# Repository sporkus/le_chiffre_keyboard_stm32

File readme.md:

# Le Chiffre Keyboard - STM32 version
-----------

Open sourced PCB originally design by tominabox1 updated to STM32 MCU.

## Design goals
* Drop-in replacement to existing cases
* MCU: STM32F072CBT6 (128Kb flash, built-in DFU bootloader) to allow more firmware features
* MX hotswap, Alps support
* Optional 36 key support

## Firmware
* [QMK and vial source](./firmware)
* [zmk config](https://github.com/petejohanson/le-chiffre-stm32-zmk-config)
* [pre-compiled vial](./firmware/le_chiffre_32_vial.bin)

To flash initially using dfu-util or qmk toolbox, plug in the board or push the reset button while DFU button is held down.

## Fabrication
* verified production files can be found [here](./pcb_production)
* pcb dimensions: 84.96x227.34mm
* SK6812 mini 3535 has placement marker on "Data In" pin. Don't confuse it with sk6812-HS mini or sk6812 mini-E.

## Misc
#### 3D assembly preview
* [online viewer](https://3dviewer.net/#model=https://github.com/sporkus/le_chiffre_keyboard_stm32/blob/main/documentation/stm32_hotswap_chiffre-3D.step)
* [step assembly](./documentation/stm32_hotswap_chiffre-3D.step)

#### PCB renders

#### BoM
[interactive BoM](./documentation/stm32_hotswap_chiffre-ibom.html)

#### Schematic
[Schematic pdf](./documentation/stm32_hotswap_chiffre-schematic.pdf)

#### Case

## Credits
tominabox1 for the [original design](https://github.com/tominabox1/Le-Chiffre-Keyboard)

## Changelog
* v0.3.0: add optional 36 key support
* v0.2.2: change center switch to soldered instead of hotswap. Group buy.
* v0.2.1: added front led bypass jumper
* v0.2.0: improved protection circuit
* v0.1: working initial prototypes

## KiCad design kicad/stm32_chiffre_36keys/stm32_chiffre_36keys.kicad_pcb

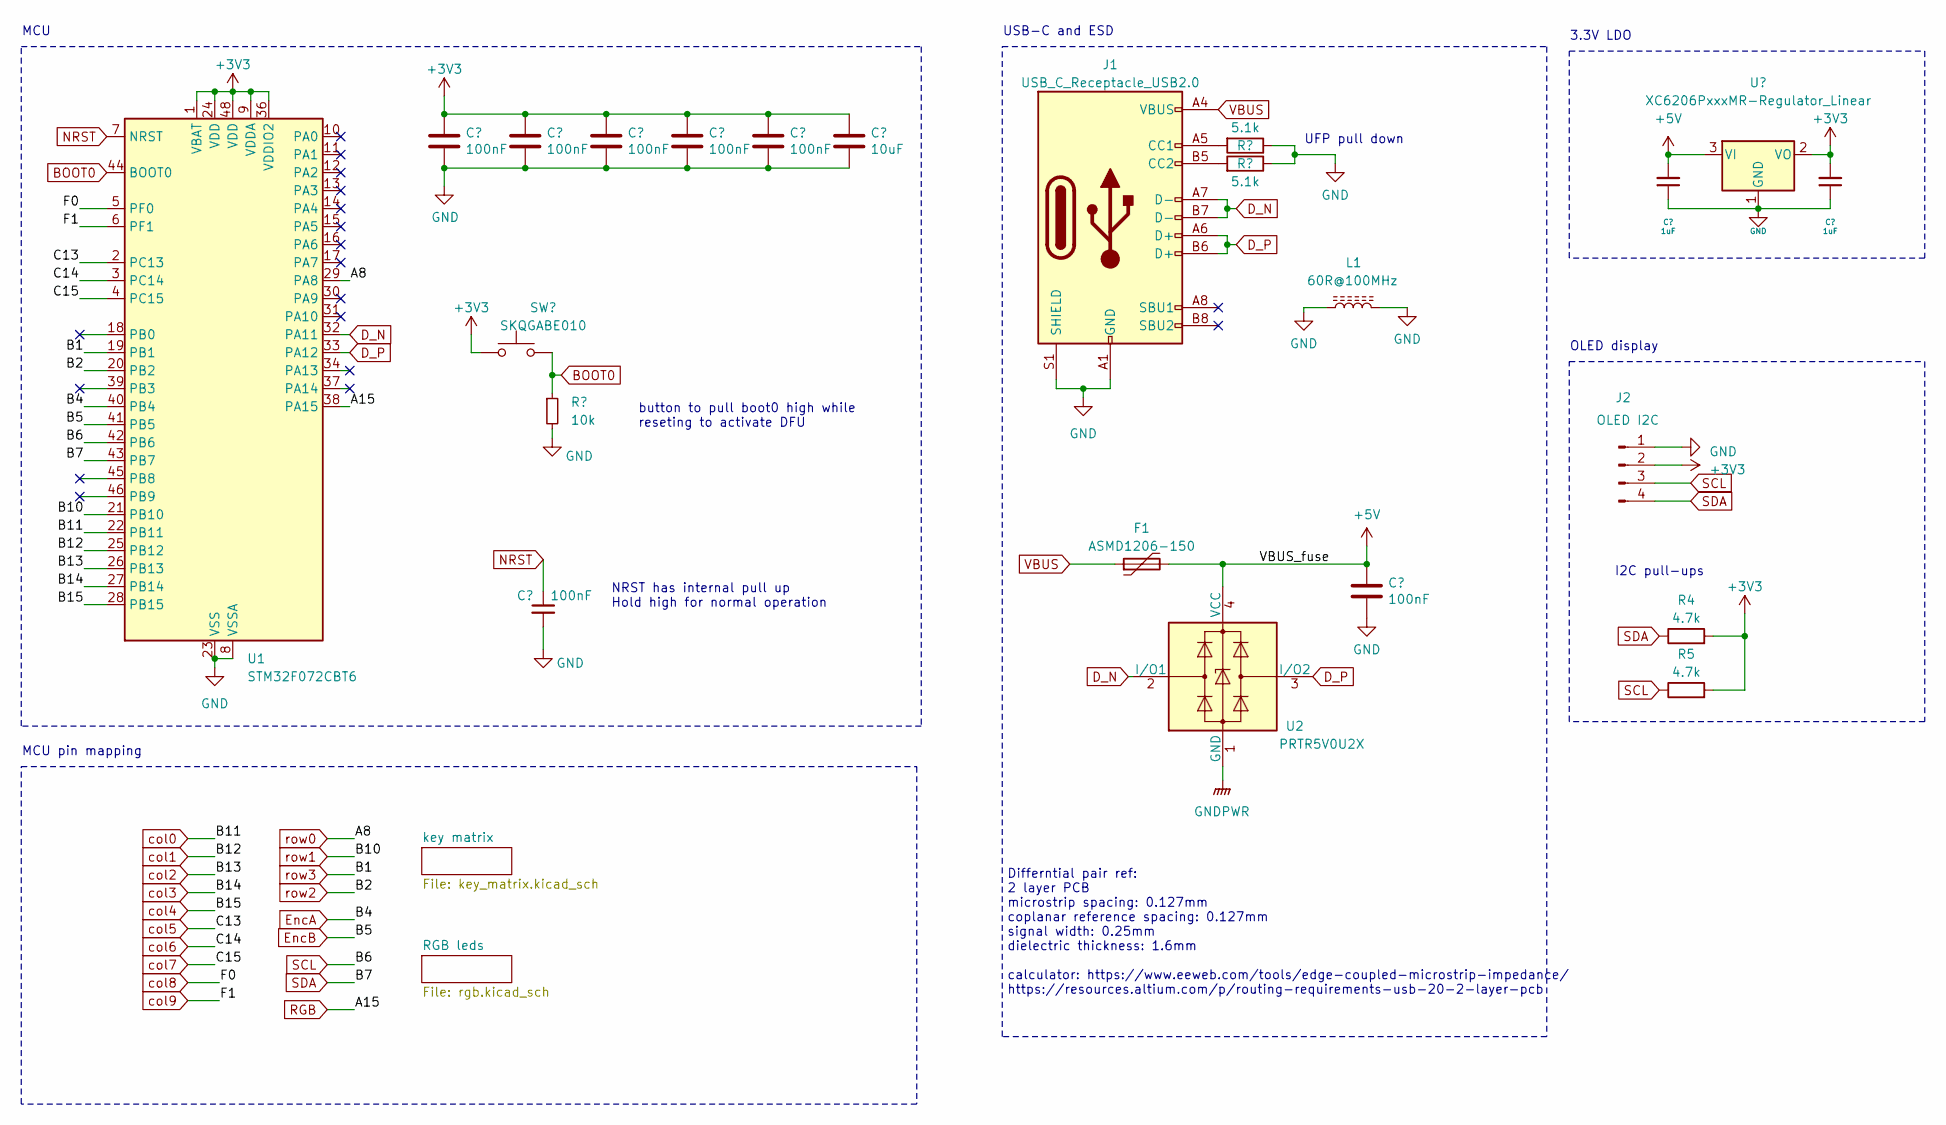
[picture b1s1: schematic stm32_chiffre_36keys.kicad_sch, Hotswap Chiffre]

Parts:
C1, C2, C3, C4, C5, C7, C8: 100nF; C_0402_1005Metric; LCSC C307331
C6: 10uF; C_0603_1608Metric
C11, C12: 1uF; C_0402_1005Metric; LCSC C52923
F1: ASMD1206-150; Fuse_1206_3216Metric; LCSC C135341
J1: USB_C_Receptacle_USB2.0; USB_C_Receptacle_HRO_TYPE-C-31-M-12; JlcRotOffset 180
J2: OLED I2C; PinHeader_1x04_P2.54mm_Vertical
L1: 60R@100MHz; L_1206_3216Metric; Manufacturer Part No MLB3216-600P4A(f); LCSC C33600
R1, R2: 5.1k; R_0402_1005Metric
R3: 10k; R_0402_1005Metric
R4, R5: 4.7k; R_0402_1005Metric
SW37: SKQGABE010; SW_SPST_SKQG_WithoutStem; LCSC C115351
U1: STM32F072CBT6; LQFP-48_7x7mm_P0.5mm; JlcRotOffset 90
U2: PRTR5V0U2X; SOT-143; LCSC C2827688
U3: XC6206PxxxMR-Regulator_Linear; SOT-23; LCSC C5446

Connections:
+3V3: C1.1, C2.1, C3.1, C4.1, C5.1, C6.1, C12.2, J2.2, R4.2, R5.2, SW37.1, U1.1 (VBAT), U1.9 (VDDA), U1.24 (VDD), U1.36 (VDDIO2), U1.48 (VDD), U3.2 (VO)
+5V: C8.1, C11.2, F1.2, U2.4 (VCC), U3.3 (VI); also elsewhere on the board
BOOT0: R3.1, SW37.2, U1.44 (BOOT0)
D_N: J1.A7 (D-), J1.B7 (D-), U1.32 (PA11), U2.2 (I/O1)
D_P: J1.A6 (D+), J1.B6 (D+), U1.33 (PA12), U2.3 (I/O2)
EncA: U1.40 (PB4); also elsewhere on the board
EncB: U1.41 (PB5); also elsewhere on the board
GND: C1.2, C2.2, C3.2, C4.2, C5.2, C6.2, C7.2, C8.2, C11.1, C12.1, J1.A1 (GND), J1.A12 (GND), J1.B1 (GND), J1.B12 (GND), J1.S1 (SHIELD), J2.1, L1.1, L1.2, R1.1, R2.1, R3.2, U1.8 (VSSA), U1.23 (VSS), U1.35 (VSS), U1.47 (VSS), U3.1 (GND); also elsewhere on the board
GNDPWR: U2.1 (GND)
NRST: C7.1, U1.7 (NRST)
unnamed: J1.A5 (CC1), R1.2
unnamed: J1.B5 (CC2), R2.2
RGB: U1.38 (PA15); also elsewhere on the board
SCL: J2.3, R5.1, U1.42 (PB6)
SDA: J2.4, R4.1, U1.43 (PB7)
VBUS: F1.1, J1.A4 (VBUS), J1.A9 (VBUS), J1.B4 (VBUS), J1.B9 (VBUS)
col0: U1.22 (PB11); also elsewhere on the board
col1: U1.25 (PB12); also elsewhere on the board
col2: U1.26 (PB13); also elsewhere on the board
col3: U1.27 (PB14); also elsewhere on the board
col4: U1.28 (PB15); also elsewhere on the board
col5: U1.2 (PC13); also elsewhere on the board
col6: U1.3 (PC14); also elsewhere on the board
col7: U1.4 (PC15); also elsewhere on the board
col8: U1.5 (PF0); also elsewhere on the board
col9: U1.6 (PF1); also elsewhere on the board
row0: U1.29 (PA8); also elsewhere on the board
row1: U1.21 (PB10); also elsewhere on the board
row2: U1.20 (PB2); also elsewhere on the board
row3: U1.19 (PB1); also elsewhere on the board

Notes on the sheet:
button to pull boot0 high while reseting to activate DFU
I2C pull-ups
UFP pull down
MCU pin mapping
MCU
3.3V LDO
USB-C and ESD
OLED display
NRST has internal pull up Hold high for normal operation
Differntial pair ref: 2 layer PCB microstrip spacing: 0.127mm coplanar reference spacing: 0.127mm signal width: 0.25mm dielectric thickness: 1.6mm calculator: https://www.eeweb.com/tools/edge-coupled-microstrip-impedance/ https://resources.altium.com/p/routing-requirements-usb-20-2-layer-pcb

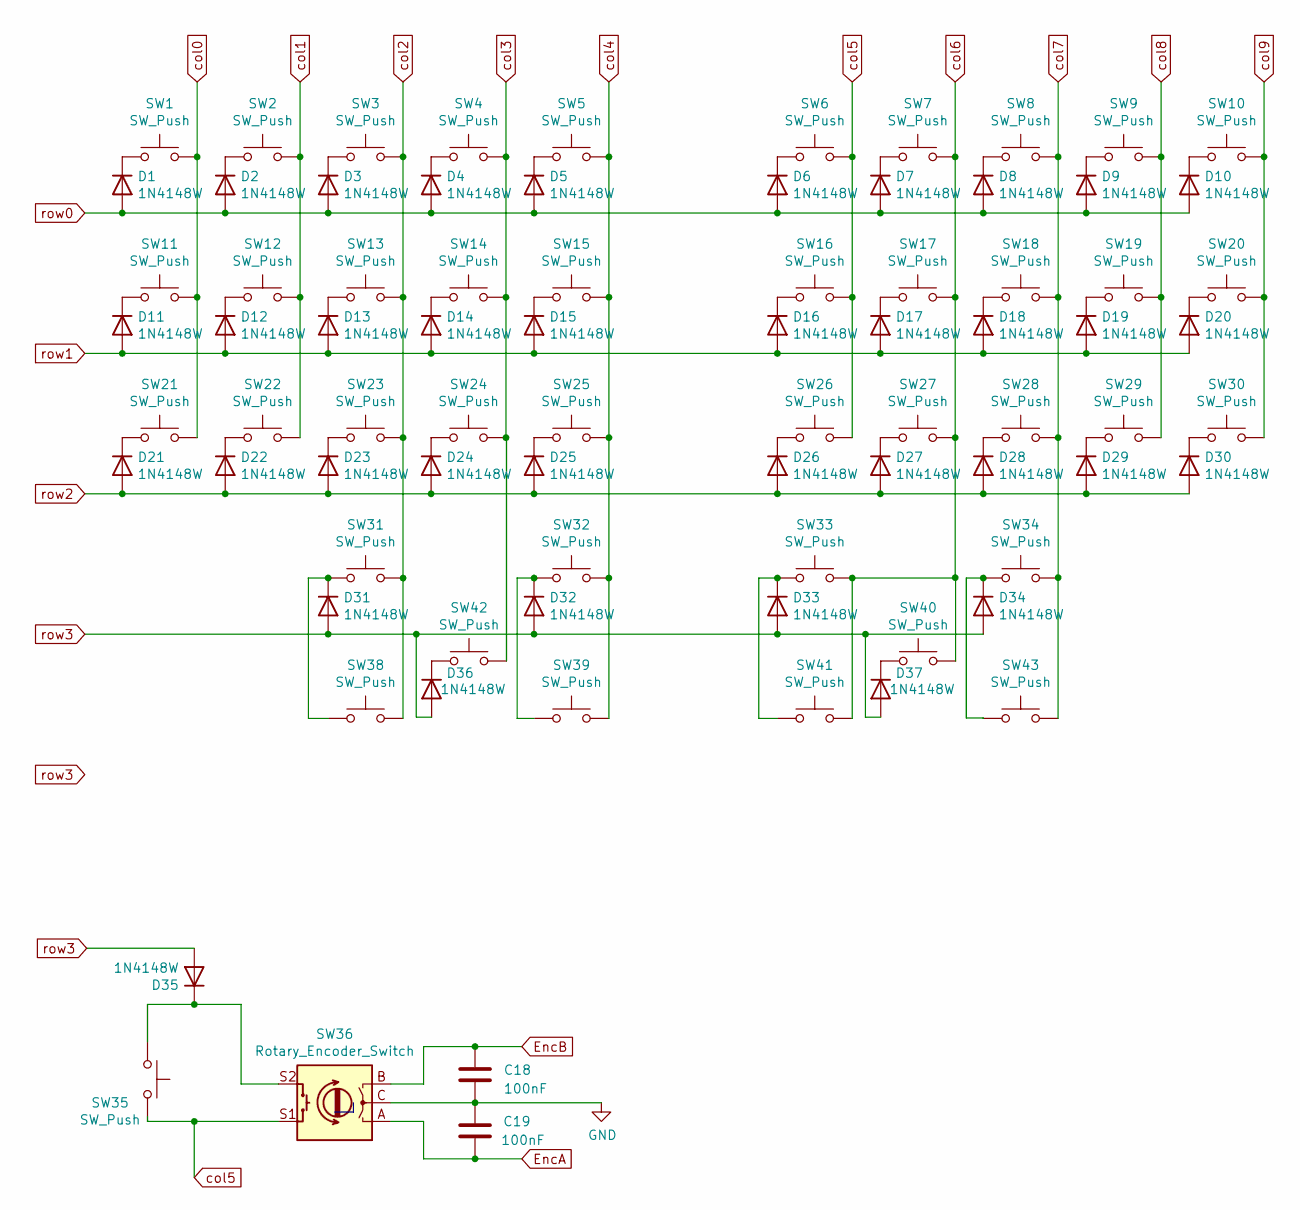
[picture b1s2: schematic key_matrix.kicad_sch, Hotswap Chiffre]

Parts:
C18, C19: 100nF; C_0402_1005Metric; LCSC C307331
D1, D2, D3, D4, D5, D11, D12, D13, D14, D15, D21, D22, D23, D24, D25, D31, D32, D36, D37: 1N4148W; D_SOD-123; JlcRotOffset 14
D6, D7, D8, D9, D10, D16, D17, D18, D19, D20, D26, D27, D28, D29, D30, D33, D34: 1N4148W; D_SOD-123; JlcRotOffset -14
D35: 1N4148W; D_SOD-123; JlcRotOffset 0
SW1, SW2, SW3, SW4, SW5, SW6, SW7, SW8, SW9, SW10, SW11, SW12, SW13, SW14, SW15, SW16, SW17, SW18, SW19, SW20, SW21, SW22, SW23, SW24, SW25, SW26, SW27, SW28, SW29, SW30, SW38, SW40, SW41, SW42: SW_Push; MX-Hotswap-Alps-1U
SW31, SW34, SW39, SW43: SW_Push; MX-Hotswap-Alps-1.25U
SW32, SW33: SW_Push; MX-Hotswap-Alps-2U
SW35: SW_Push; MX-Alps-Hybrid-1U
SW36: Rotary_Encoder_Switch; RotaryEncoder_EC11_no_mp

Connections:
EncA: SW36.A; also elsewhere on the board
EncB: SW36.B; also elsewhere on the board
GND: SW36.C; also elsewhere on the board
unnamed: D1.1 (K), SW1.1
unnamed: D2.1 (K), SW2.1
unnamed: D3.1 (K), SW3.1
unnamed: D4.1 (K), SW4.1
unnamed: D5.1 (K), SW5.1
unnamed: D6.1 (K), SW6.1
unnamed: D7.1 (K), SW7.1
unnamed: D8.1 (K), SW8.1
unnamed: D9.1 (K), SW9.1
unnamed: D10.1 (K), SW10.1
unnamed: D11.1 (K), SW11.1
unnamed: D12.1 (K), SW12.1
unnamed: D13.1 (K), SW13.1
unnamed: D14.1 (K), SW14.1
unnamed: D15.1 (K), SW15.1
unnamed: D16.1 (K), SW16.1
unnamed: D17.1 (K), SW17.1
unnamed: D18.1 (K), SW18.1
unnamed: D19.1 (K), SW19.1
unnamed: D20.1 (K), SW20.1
unnamed: D21.1 (K), SW21.1
unnamed: D22.1 (K), SW22.1
unnamed: D23.1 (K), SW23.1
unnamed: D24.1 (K), SW24.1
unnamed: D25.1 (K), SW25.1
unnamed: D26.1 (K), SW26.1
unnamed: D27.1 (K), SW27.1
unnamed: D28.1 (K), SW28.1
unnamed: D29.1 (K), SW29.1
unnamed: D30.1 (K), SW30.1
unnamed: D31.1 (K), SW31.1, SW38.2
unnamed: D32.1 (K), SW32.1, SW39.2
unnamed: D33.1 (K), SW33.1, SW41.2
unnamed: D34.1 (K), SW34.2, SW43.1
unnamed: D35.1 (K), SW35.1, SW36.S2
unnamed: D36.1 (K), SW42.1
unnamed: D37.1 (K), SW40.1
col0: SW1.2, SW11.2, SW21.2; also elsewhere on the board
col1: SW2.2, SW12.2, SW22.2; also elsewhere on the board
col2: SW3.2, SW13.2, SW23.2, SW31.2, SW38.1; also elsewhere on the board
col3: SW4.2, SW14.2, SW24.2, SW42.2; also elsewhere on the board
col4: SW5.2, SW15.2, SW25.2, SW32.2, SW39.1; also elsewhere on the board
col5: SW6.2, SW16.2, SW26.2, SW35.2, SW36.S1; also elsewhere on the board
col6: SW7.2, SW17.2, SW27.2, SW33.2, SW40.2, SW41.1; also elsewhere on the board
col7: SW8.2, SW18.2, SW28.2, SW34.1, SW43.2; also elsewhere on the board
col8: SW9.2, SW19.2, SW29.2; also elsewhere on the board
col9: SW10.2, SW20.2, SW30.2; also elsewhere on the board
row0: D1.2 (A), D2.2 (A), D3.2 (A), D4.2 (A), D5.2 (A), D6.2 (A), D7.2 (A), D8.2 (A), D9.2 (A), D10.2 (A); also elsewhere on the board
row1: D11.2 (A), D12.2 (A), D13.2 (A), D14.2 (A), D15.2 (A), D16.2 (A), D17.2 (A), D18.2 (A), D19.2 (A), D20.2 (A); also elsewhere on the board
row2: D21.2 (A), D22.2 (A), D23.2 (A), D24.2 (A), D25.2 (A), D26.2 (A), D27.2 (A), D28.2 (A), D29.2 (A), D30.2 (A); also elsewhere on the board
row3: D31.2 (A), D32.2 (A), D33.2 (A), D34.2 (A), D35.2 (A), D36.2 (A), D37.2 (A); also elsewhere on the board

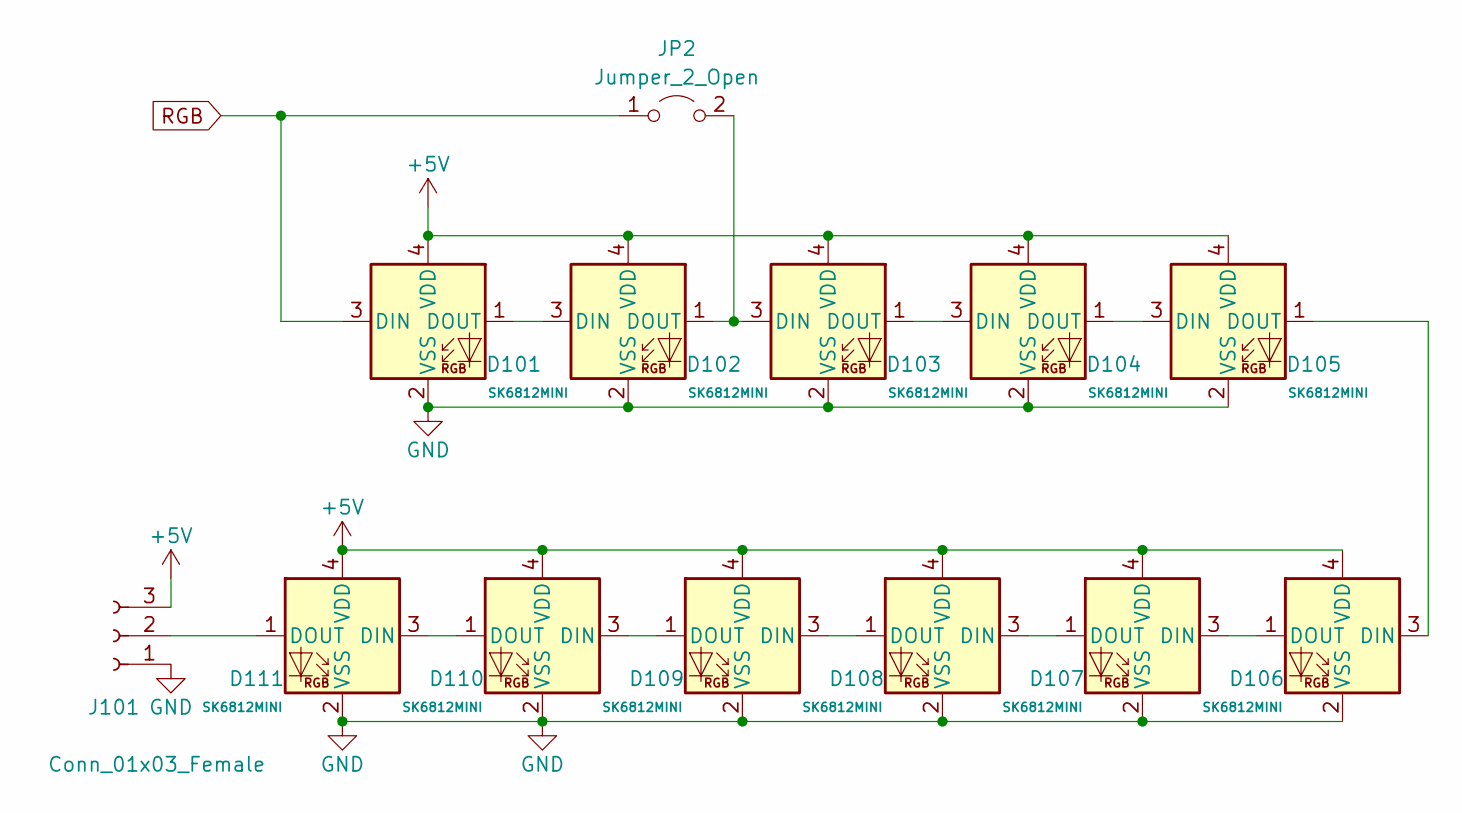
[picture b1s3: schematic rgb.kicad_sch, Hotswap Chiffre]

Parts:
D101, D102: SK6812MINI; LED_SK6812MINI_PLCC4_3.5x3.5mm_P1.75mm
D103, D105, D106: SK6812MINI; LED_SK6812MINI_PLCC4_3.5x3.5mm_P1.75mm; JlcRotOffset -14
D104: SK6812MINI; LED_SK6812MINI_PLCC4_3.5x3.5mm_P1.75mm; JlcRotOffset 166
D107: SK6812MINI; LED_SK6812MINI_PLCC4_3.5x3.5mm_P1.75mm; JlcRotOffset 180
D108, D109, D111: SK6812MINI; LED_SK6812MINI_PLCC4_3.5x3.5mm_P1.75mm; JlcRotOffset 14
D110: SK6812MINI; LED_SK6812MINI_PLCC4_3.5x3.5mm_P1.75mm; JlcRotOffset 194
J101: Conn_01x03_Female; PinSocket_1x03_P2.54mm_Vertical
JP2: Jumper_2_Open; SolderJumper-2_P1.3mm_Open_TrianglePad1.0x1.5mm

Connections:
+5V: D101.4 (VDD), D102.4 (VDD), D103.4 (VDD), D104.4 (VDD), D105.4 (VDD), D106.4 (VDD), D107.4 (VDD), D108.4 (VDD), D109.4 (VDD), D110.4 (VDD), D111.4 (VDD), J101.3 (Pin_1); also elsewhere on the board
GND: D101.2 (VSS), D102.2 (VSS), D103.2 (VSS), D104.2 (VSS), D105.2 (VSS), D106.2 (VSS), D107.2 (VSS), D108.2 (VSS), D109.2 (VSS), D110.2 (VSS), D111.2 (VSS), J101.1 (Pin_3); also elsewhere on the board
unnamed: D101.1 (DOUT), D102.3 (DIN)
unnamed: D102.1 (DOUT), D103.3 (DIN), JP2.2 (B)
unnamed: D103.1 (DOUT), D104.3 (DIN)
unnamed: D104.1 (DOUT), D105.3 (DIN)
unnamed: D105.1 (DOUT), D106.3 (DIN)
unnamed: D106.1 (DOUT), D107.3 (DIN)
unnamed: D107.1 (DOUT), D108.3 (DIN)
unnamed: D108.1 (DOUT), D109.3 (DIN)
unnamed: D109.1 (DOUT), D110.3 (DIN)
unnamed: D110.1 (DOUT), D111.3 (DIN)
unnamed: D111.1 (DOUT), J101.2
RGB: D101.3 (DIN), JP2.1 (A); also elsewhere on the board

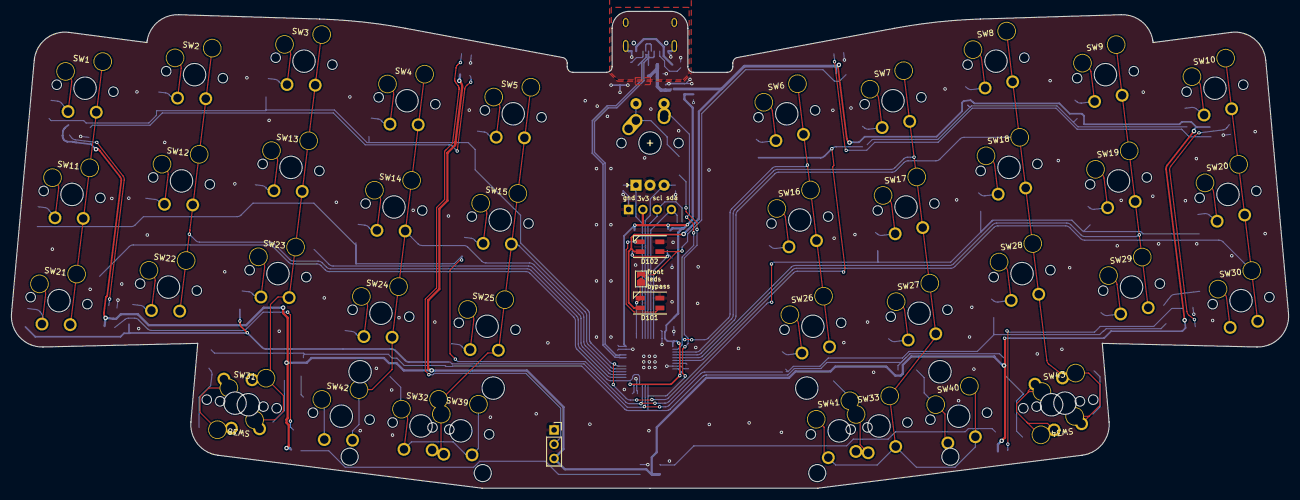
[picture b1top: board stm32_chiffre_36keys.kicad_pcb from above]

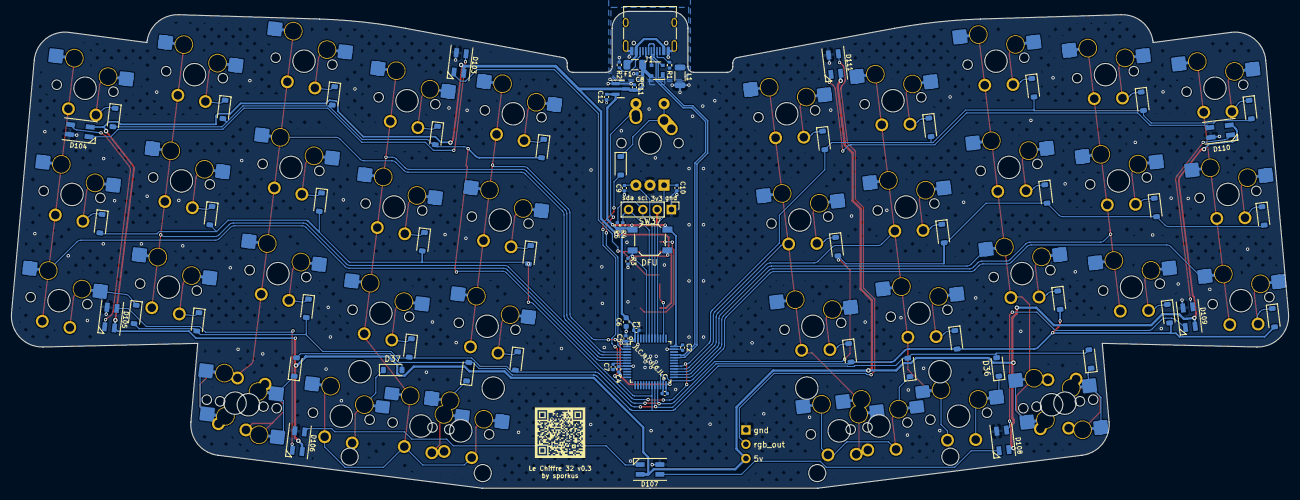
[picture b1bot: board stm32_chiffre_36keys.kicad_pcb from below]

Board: 2 copper layers, 227.4 x 84.9 mm, 117 parts (71 on the bottom side), 77 nets.

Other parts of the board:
C9, C10: 100nF; C_0402_1005Metric

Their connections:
EncA: C10.1; also elsewhere on the board
EncB: C9.1; also elsewhere on the board
GND: C9.2, C10.2; also elsewhere on the board

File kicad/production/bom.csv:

Designator,Footprint,Quantity,Value,LCSC Part #
"C1, C10, C2, C3, C4, C5, C7, C8, C9",0402,9,100nF,C307331
"C11, C12",0402,2,1uF,C52923
C6,0603,1,10uF,
"D1, D10, D11, D12, D13, D14, D15, D16, D17, D18, D19, D2, D20, D21, D22, D23, D24, D25, D26, D27, D28, D29, D3, D30, D31, D32, D33, D34, D35, D4, D5, D6, D7, D8, D9",D_SOD-123,35,1N4148W,
"D101, D102, D103, D104, D105, D106, D107, D108, D109, D110, D111",LED_SK6812MINI_PLCC4_3.5x3.5mm_P1.75mm,11,SK6812MINI,
F1,1206,1,ASMD1206-150,C135341
J1,USB_C_Receptacle_HRO_TYPE-C-31-M-12,1,USB_C_Receptacle_USB2.0,
J101,PinSocket_1x03_P2.54mm_Vertical,1,Conn_01x03_Female,
L1,1206,1,60R@100MHz,C33600
"R1, R2",0402,2,5.1k,
R3,0402,1,10k,
"R4, R5",0402,2,4.7k,
"SW1, SW10, SW11, SW12, SW13, SW14, SW15, SW16, SW17, SW18, SW19, SW2, SW20, SW21, SW22, SW23, SW24, SW25, SW26, SW27, SW28, SW29, SW3, SW30, SW35, SW4, SW5, SW6, SW7, SW8, SW9",MX-Hotswap-Alps-1U,31,SW_Push,
"SW31, SW34",MX-Hotswap-Alps-1.25U,2,SW_Push,
"SW32, SW33",MX-Hotswap-Alps-2U,2,SW_Push,
SW37,SW_SPST_SKQG_WithoutStem,1,SKQGABE010,C115351
U1,LQFP-48_7x7mm_P0.5mm,1,STM32F072CBT6,
U2,SOT-143,1,PRTR5V0U2X,C2827688
U3,SOT-23,1,XC6206PxxxMR-Regulator_Linear,C5446

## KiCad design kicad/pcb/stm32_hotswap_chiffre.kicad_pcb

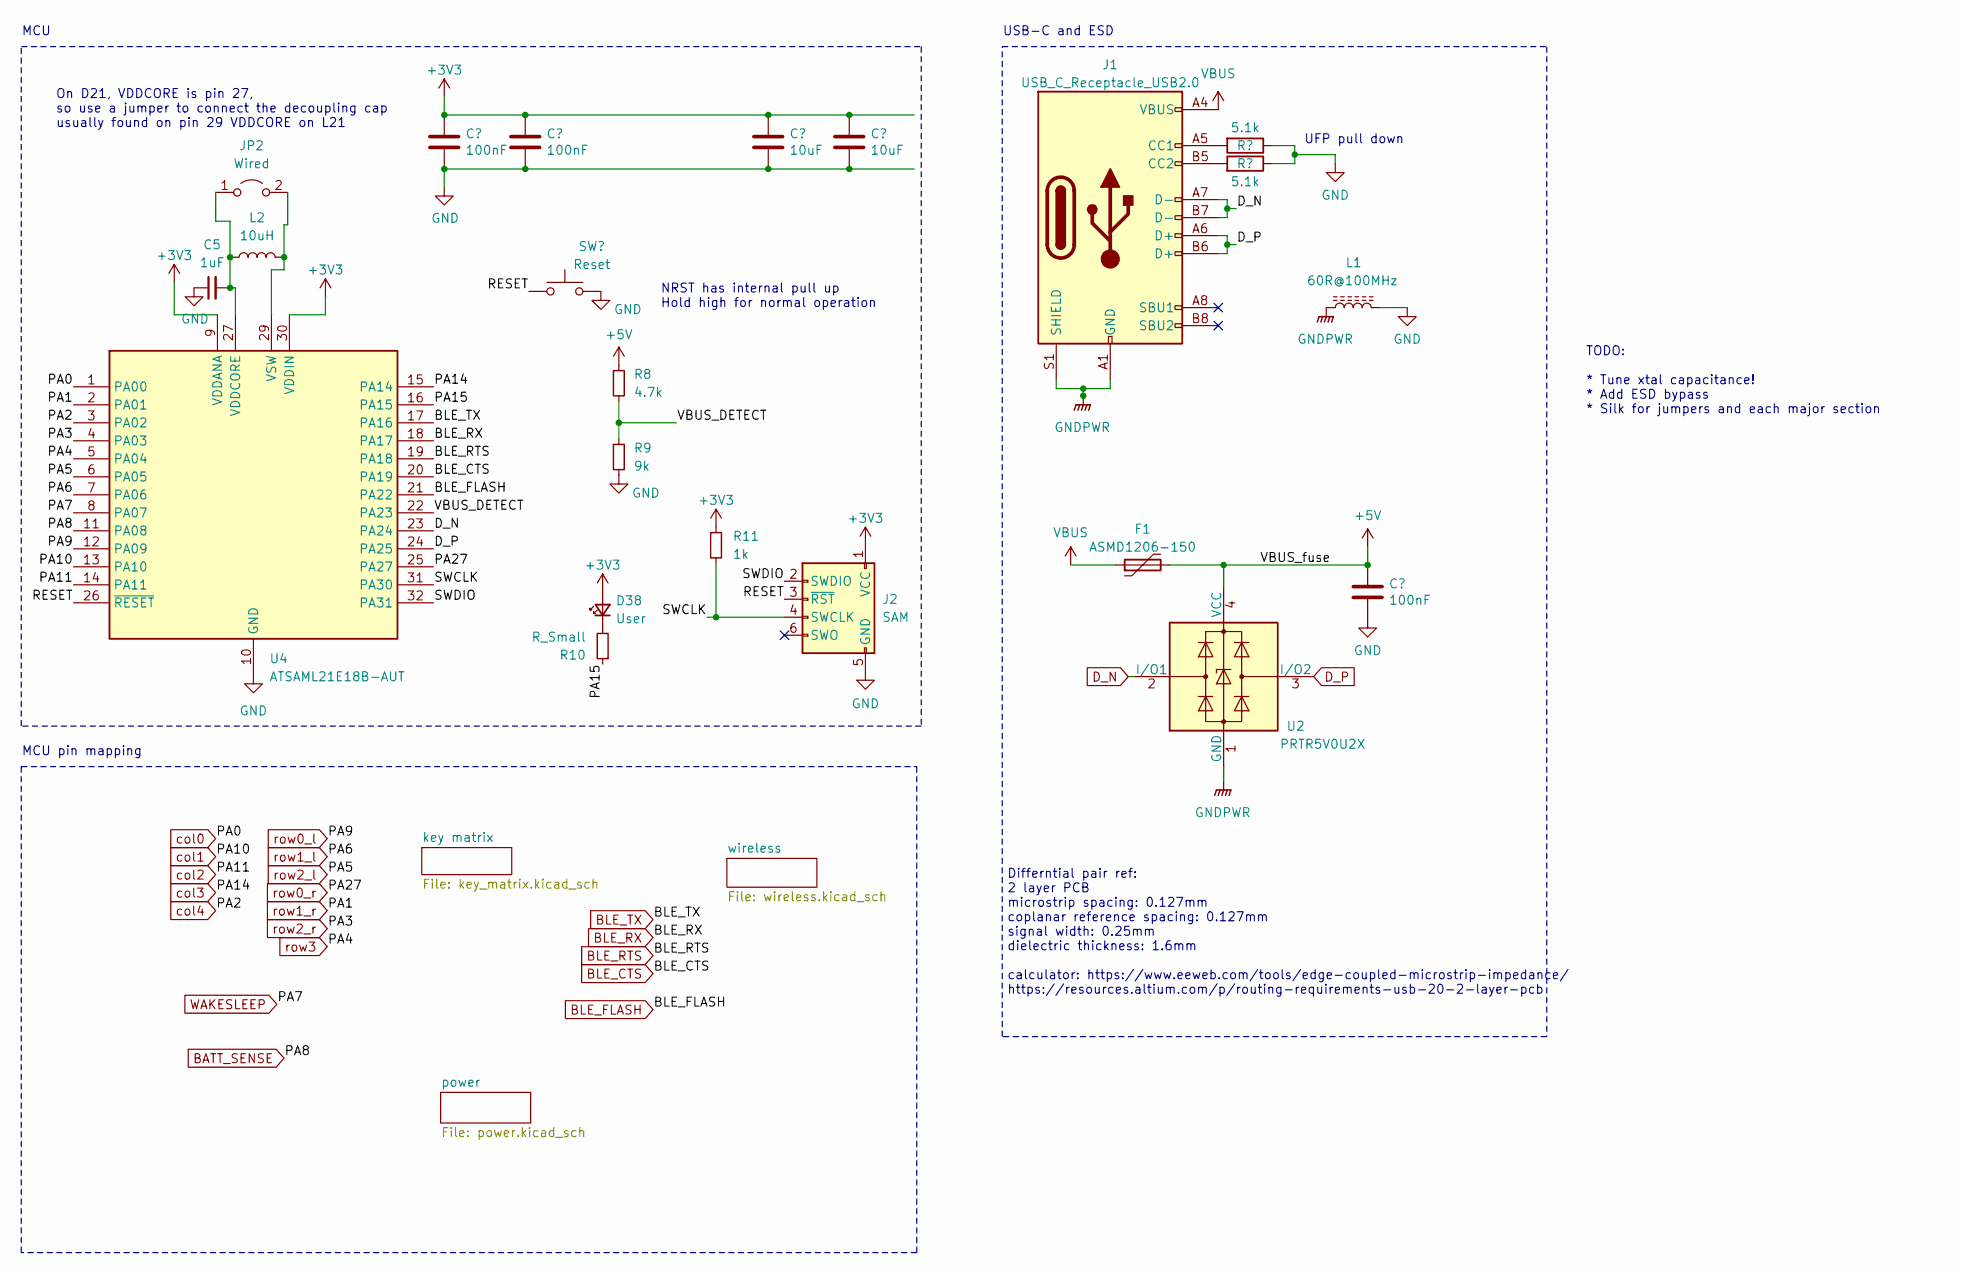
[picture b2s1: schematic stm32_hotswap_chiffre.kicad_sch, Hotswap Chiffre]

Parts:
C1, C2, C8: 100nF; C_0805_2012Metric; LCSC C307331
C3: 10uF; C_0805_2012Metric; LCSC C307331
C4: 10uF; C_0805_2012Metric
C5: 1uF; C_0805_2012Metric
D38: User; LED_0805_2012Metric
F1: ASMD1206-150; Fuse_1206_3216Metric; LCSC C135341
J1: USB_C_Receptacle_USB2.0; USB_C_Receptacle_HRO_TYPE-C-31-M-12; JlcRotOffset 180
J2: SAM; CON_TC2030_outlined
JP2: Wired; SolderJumper-2_P1.3mm_Open_TrianglePad1.0x1.5mm
L1: 60R@100MHz; L_1206_3216Metric; Manufacturer Part No MLB3216-600P4A(f); LCSC C33600
L2: 10uH; L_0805_2012Metric; LCSC Part Number C2932309
R1, R2: 5.1k; R_0805_2012Metric
R8: 4.7k; R_0805_2012Metric
R9: 9k; R_0805_2012Metric
R10: R_Small; R_0805_2012Metric
R11: 1k; R_0805_2012Metric
SW37: Reset; SW_SPST_SKQG_WithoutStem; MPN SKQGABE010; LCSC C115351
U2: PRTR5V0U2X; SOT-143; LCSC C2827688
U4: ATSAML21E18B-AUT; TQFP-32_7x7mm_P0.8mm

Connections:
+5V: C8.1, F1.2, R8.1, U2.4 (VCC); also elsewhere on the board
/PA15: R10.1, U4.16 (PA15)
/RESET: J2.3 (~RST), SW37.1, U4.26 (~RESET)
/SWCLK: J2.4 (SWCLK), R11.2, U4.31 (PA30)
/SWDIO: J2.2 (SWDIO), U4.32 (PA31)
/VBUS_DETECT: R8.2, R9.1, U4.22 (PA23)
BATT_SENSE: U4.11 (PA08); also elsewhere on the board
BLE_CTS: U4.20 (PA19); also elsewhere on the board
BLE_FLASH: U4.21 (PA22); also elsewhere on the board
BLE_RTS: U4.19 (PA18); also elsewhere on the board
BLE_RX: U4.18 (PA17); also elsewhere on the board
BLE_TX: U4.17 (PA16); also elsewhere on the board
D_N: J1.A7 (D-), J1.B7 (D-), U2.2 (I/O1), U4.23 (PA24)
D_P: J1.A6 (D+), J1.B6 (D+), U2.3 (I/O2), U4.24 (PA25)
GNDPWR: J1.A1 (GND), J1.A12 (GND), J1.B1 (GND), J1.B12 (GND), J1.S1 (SHIELD), L1.1, U2.1 (GND)
unnamed: D38.1 (K), R10.2
unnamed: J1.A5 (CC1), R1.2
unnamed: J1.B5 (CC2), R2.2
unnamed: C5.2, JP2.1 (A), L2.1, U4.27 (VDDCORE)
unnamed: JP2.2 (B), L2.2, U4.29 (VSW)
VBUS: F1.1, J1.A4 (VBUS), J1.A9 (VBUS), J1.B4 (VBUS), J1.B9 (VBUS)
WAKESLEEP: U4.8 (PA07); also elsewhere on the board
col0: U4.1 (PA00); also elsewhere on the board
col1: U4.13 (PA10); also elsewhere on the board
col2: U4.14 (PA11); also elsewhere on the board
col3: U4.15 (PA14); also elsewhere on the board
col4: U4.3 (PA02); also elsewhere on the board
row0_l: U4.12 (PA09); also elsewhere on the board
row0_r: U4.25 (PA27); also elsewhere on the board
row1_l: U4.7 (PA06); also elsewhere on the board
row1_r: U4.2 (PA01); also elsewhere on the board
row2_l: U4.6 (PA05); also elsewhere on the board
row2_r: U4.4 (PA03); also elsewhere on the board
row3: U4.5 (PA04); also elsewhere on the board

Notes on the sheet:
On D21, VDDCORE is pin 27, so use a jumper to connect the decoupling cap usually found on pin 29 VDDCORE on L21
UFP pull down
MCU pin mapping
TODO: * Tune xtal capacitance! * Add ESD bypass * Silk for jumpers and each major section
MCU
USB-C and ESD
NRST has internal pull up Hold high for normal operation
Differntial pair ref: 2 layer PCB microstrip spacing: 0.127mm coplanar reference spacing: 0.127mm signal width: 0.25mm dielectric thickness: 1.6mm calculator: https://www.eeweb.com/tools/edge-coupled-microstrip-impedance/ https://resources.altium.com/p/routing-requirements-usb-20-2-layer-pcb

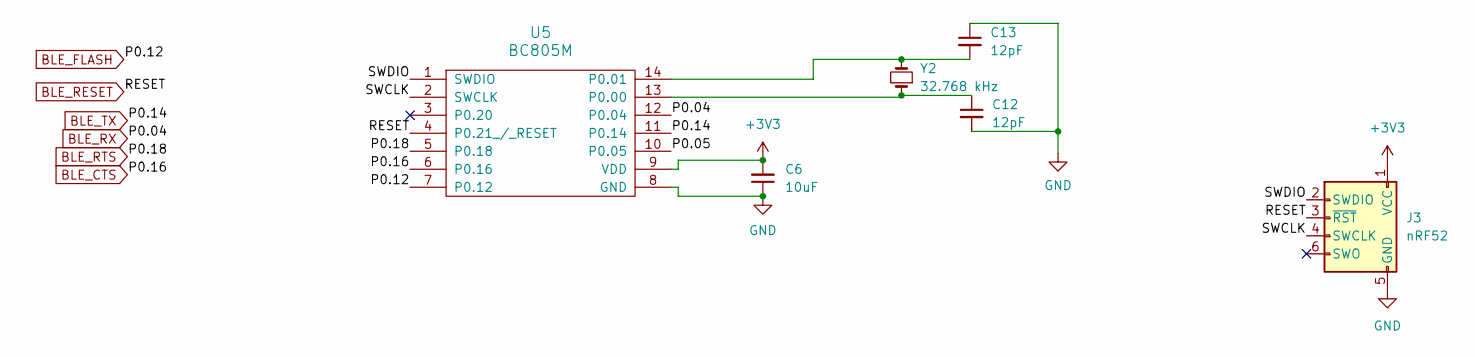
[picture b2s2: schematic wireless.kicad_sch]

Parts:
C6: 10uF; C_0805_2012Metric
C12, C13: 12pF; C_0805_2012Metric
J3: nRF52; CON_TC2030_outlined
U5: BC805M
Y2: 32.768 kHz; Crystal_SMD_2012-2Pin_2.0x1.2mm_HandSoldering

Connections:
/wireless/P0.05: U5.10 (P0.05)
/wireless/SWCLK: J3.4 (SWCLK), U5.2 (SWCLK)
/wireless/SWDIO: J3.2 (SWDIO), U5.1 (SWDIO)
BLE_CTS: U5.6 (P0.16); also elsewhere on the board
BLE_FLASH: U5.7 (P0.12); also elsewhere on the board
BLE_RESET: J3.3 (~RST), U5.4 (P0.21_/_RESET)
BLE_RTS: U5.5 (P0.18); also elsewhere on the board
BLE_RX: U5.12 (P0.04); also elsewhere on the board
BLE_TX: U5.11 (P0.14); also elsewhere on the board
unnamed: C13.2, U5.14 (P0.01), Y2.2

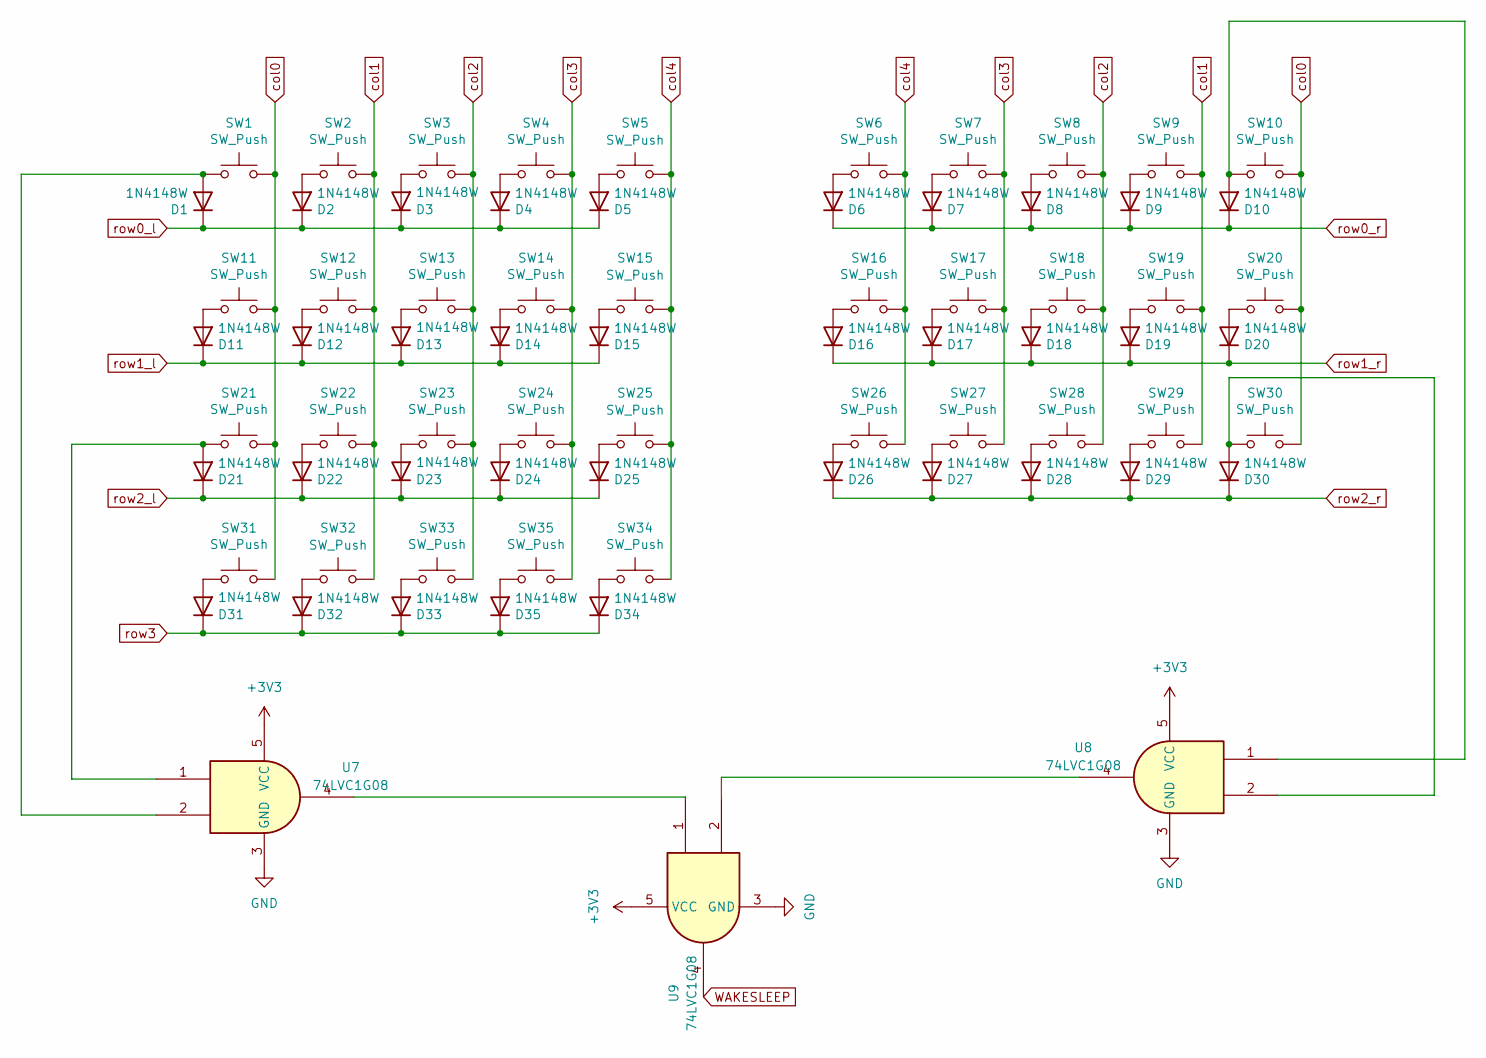
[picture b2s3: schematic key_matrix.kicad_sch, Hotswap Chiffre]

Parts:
D1, D2, D3, D4, D5, D11, D12, D13, D14, D15, D21, D22, D23, D24, D25, D31, D32: 1N4148W; D_SOD-123; JlcRotOffset 14
D6, D7, D8, D9, D10, D16, D17, D18, D19, D20, D26, D27, D28, D29, D30, D33, D34, D35: 1N4148W; D_SOD-123; JlcRotOffset -14
SW1, SW2, SW3, SW4, SW5, SW6, SW7, SW8, SW9, SW10, SW11, SW12, SW13, SW14, SW15, SW16, SW17, SW18, SW19, SW20, SW21, SW22, SW23, SW24, SW25, SW26, SW27, SW28, SW29, SW30, SW33: SW_Push; MX-Hotswap-Alps-1U
SW31, SW34: SW_Push; MX-Hotswap-Alps-1.25U
SW32, SW35: SW_Push; MX-Hotswap-Alps-2U
U7, U8, U9: 74LVC1G08; SOT-23-5_HandSoldering

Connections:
unnamed: D1.2 (A), SW1.1, U7.2
unnamed: D2.2 (A), SW2.1
unnamed: D3.2 (A), SW3.1
unnamed: D4.2 (A), SW4.1
unnamed: D5.2 (A), SW5.1
unnamed: D6.2 (A), SW6.1
unnamed: D7.2 (A), SW7.1
unnamed: D8.2 (A), SW8.1
unnamed: D9.2 (A), SW9.1
unnamed: D10.2 (A), SW10.1, U8.1
unnamed: D11.2 (A), SW11.1
unnamed: D12.2 (A), SW12.1
unnamed: D13.2 (A), SW13.1
unnamed: D14.2 (A), SW14.1
unnamed: D15.2 (A), SW15.1
unnamed: D16.2 (A), SW16.1
unnamed: D17.2 (A), SW17.1
unnamed: D18.2 (A), SW18.1
unnamed: D19.2 (A), SW19.1
unnamed: D20.2 (A), SW20.1
unnamed: D21.2 (A), SW21.1, U7.1
unnamed: D22.2 (A), SW22.1
unnamed: D23.2 (A), SW23.1
unnamed: D24.2 (A), SW24.1
unnamed: D25.2 (A), SW25.1
unnamed: D26.2 (A), SW26.1
unnamed: D27.2 (A), SW27.1
unnamed: D28.2 (A), SW28.1
unnamed: D29.2 (A), SW29.1
unnamed: D30.2 (A), SW30.1, U8.2
unnamed: D31.2 (A), SW31.1
unnamed: D32.2 (A), SW32.1
unnamed: D33.2 (A), SW33.1
unnamed: D34.2 (A), SW34.1
unnamed: D35.2 (A), SW35.1
unnamed: U7.4, U9.1
unnamed: U8.4, U9.2
WAKESLEEP: U9.4; also elsewhere on the board
col0: SW1.2, SW10.2, SW11.2, SW20.2, SW21.2, SW30.2, SW31.2; also elsewhere on the board
col1: SW2.2, SW9.2, SW12.2, SW19.2, SW22.2, SW29.2, SW32.2; also elsewhere on the board
col2: SW3.2, SW8.2, SW13.2, SW18.2, SW23.2, SW28.2, SW33.2; also elsewhere on the board
col3: SW4.2, SW7.2, SW14.2, SW17.2, SW24.2, SW27.2, SW35.2; also elsewhere on the board
col4: SW5.2, SW6.2, SW15.2, SW16.2, SW25.2, SW26.2, SW34.2; also elsewhere on the board
row0_l: D1.1 (K), D2.1 (K), D3.1 (K), D4.1 (K), D5.1 (K); also elsewhere on the board
row0_r: D6.1 (K), D7.1 (K), D8.1 (K), D9.1 (K), D10.1 (K); also elsewhere on the board
row1_l: D11.1 (K), D12.1 (K), D13.1 (K), D14.1 (K), D15.1 (K); also elsewhere on the board
row1_r: D16.1 (K), D17.1 (K), D18.1 (K), D19.1 (K), D20.1 (K); also elsewhere on the board
row2_l: D21.1 (K), D22.1 (K), D23.1 (K), D24.1 (K), D25.1 (K); also elsewhere on the board
row2_r: D26.1 (K), D27.1 (K), D28.1 (K), D29.1 (K), D30.1 (K); also elsewhere on the board
row3: D31.1 (K), D32.1 (K), D33.1 (K), D34.1 (K), D35.1 (K); also elsewhere on the board

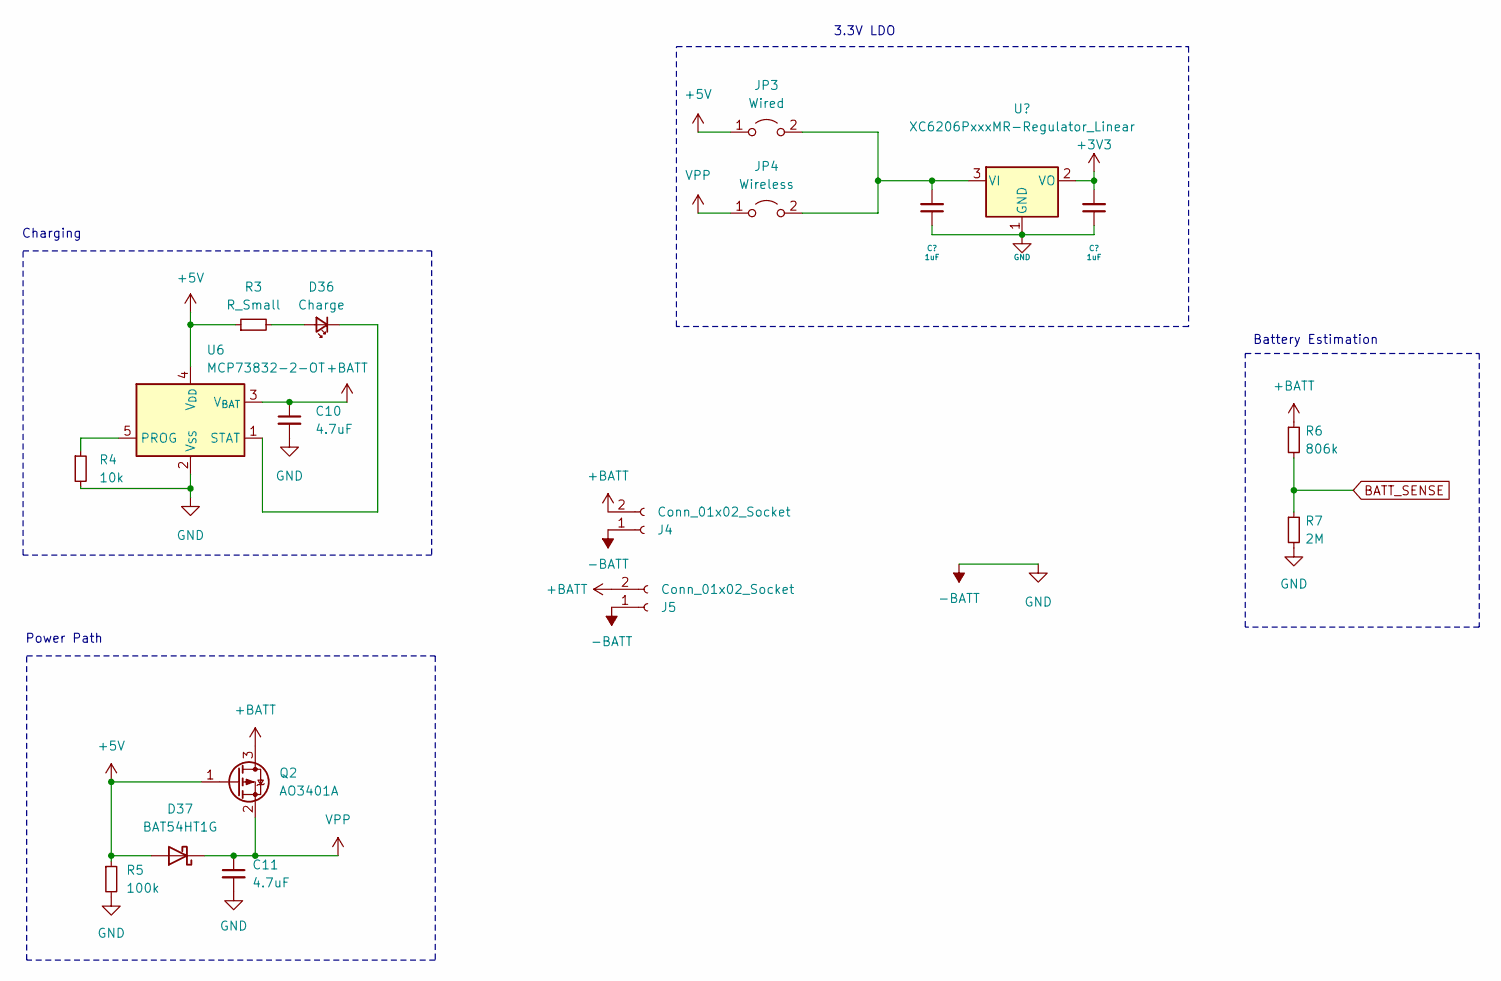
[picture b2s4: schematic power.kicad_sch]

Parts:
C10, C11: 4.7uF; C_0805_2012Metric
C12: 1uF; C_0805_2012Metric; LCSC C52923
D36: Charge; LED_0805_2012Metric
D37: BAT54HT1G; D_SOD-323
J4: Conn_01x02_Socket; JST_SH_BM02B-SRSS-TB_1x02-1MP_P1.00mm_Vertical
J5: Conn_01x02_Socket; PinHeader_1x02_P2.54mm_Vertical
JP3: Wired; SolderJumper-2_P1.3mm_Open_TrianglePad1.0x1.5mm
JP4: Wireless; SolderJumper-2_P1.3mm_Open_TrianglePad1.0x1.5mm
Q2: AO3401A; SOT-23
R3: R_Small; R_0805_2012Metric
R4: 10k; R_0805_2012Metric
R5: 100k; R_0805_2012Metric
R6: 806k; R_0805_2012Metric
R7: 2M; R_0805_2012Metric
U3: XC6206PxxxMR-Regulator_Linear; SOT-23; LCSC C5446
U6: MCP73832-2-OT; SOT-23-5

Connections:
+5V: D37.2 (A), JP3.1 (A), Q2.1 (G), R3.1, R5.1, U6.4 (V_{DD}); also elsewhere on the board
+BATT: C10.1, J4.2, J5.2, Q2.3 (D), R6.1, U6.3 (V_{BAT})
BATT_SENSE: R6.2, R7.1; also elsewhere on the board
unnamed: D36.2 (A), R3.2
unnamed: D36.1 (K), U6.1 (STAT)
unnamed: R4.1, U6.5 (PROG)

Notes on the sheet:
Power Path
3.3V LDO
Battery Estimation
Charging

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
